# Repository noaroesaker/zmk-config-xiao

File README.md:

# zmk_corne

This project would not be possible without the help of these people:
https://github.com/makgyber/kiai-split
https://github.com/wj-zhe/Kretstrad
or most importantly:
https://github.com/alexpantiukhin/zmk-config-xiao
This one helped me figure out the layout for the files i need to make the firmware compile. It is modified, but the core of this persons work is still there, so thanks.

But lets not forget the best layout for custom keyboards :)
https://github.com/foostan/crkbd

And also the youtubers who helped me understand:
https://www.youtube.com/@joe_scotto
https://www.youtube.com/@SethusBuilds
https://www.youtube.com/@BenVallacksKeyboards
https://www.youtube.com/@BenVallack

This corne like build features a Xiao BLE controller and a custom designed board designed by me, but heavily inspired by the crkbd.
The wiring based on how the kiai split does it to keep both controllers up side but not use multiple pads like the older cornes or the helix

KiCad project is a redesigned corne choc, but everything is changed except the general outline. Files in this repository

The PCB did work, but there is some clearance issues with the power switch and the controller, so that will be changed in the kicad folder.

battery test:
10 nov 22:53:31 L = 3,89V R = 3,89V
+ 10:45 (battery connected) =
11 nov 09:46:10 L = 3,85V R = 3,86V
+ 02:30 (youtube usage) =
11 nov 12:15:10 L = 3,84V R = 3,85V
+ 01:30 (youtube and 10 min osu) =
11 nov 13:42:30 L = 3,83V R = 3,84V
+ 10:00 (disconnect battery) =
12 nov 11:48:30 L = 3,83V R = 3,85V
+ 08:45 (youtube usage) =
12 nov 20:27:30 L = 3,79V R = 3,82V

avrg loss
  L = 0,004V/h
  R = 0,003V/h

estimated battery life (4,1V - 3,2V = 0,9V)
  L = 0,9V / 0,004V = 225h = 9 days
  R = 0,9V / 0,003V = 300h = 12 days

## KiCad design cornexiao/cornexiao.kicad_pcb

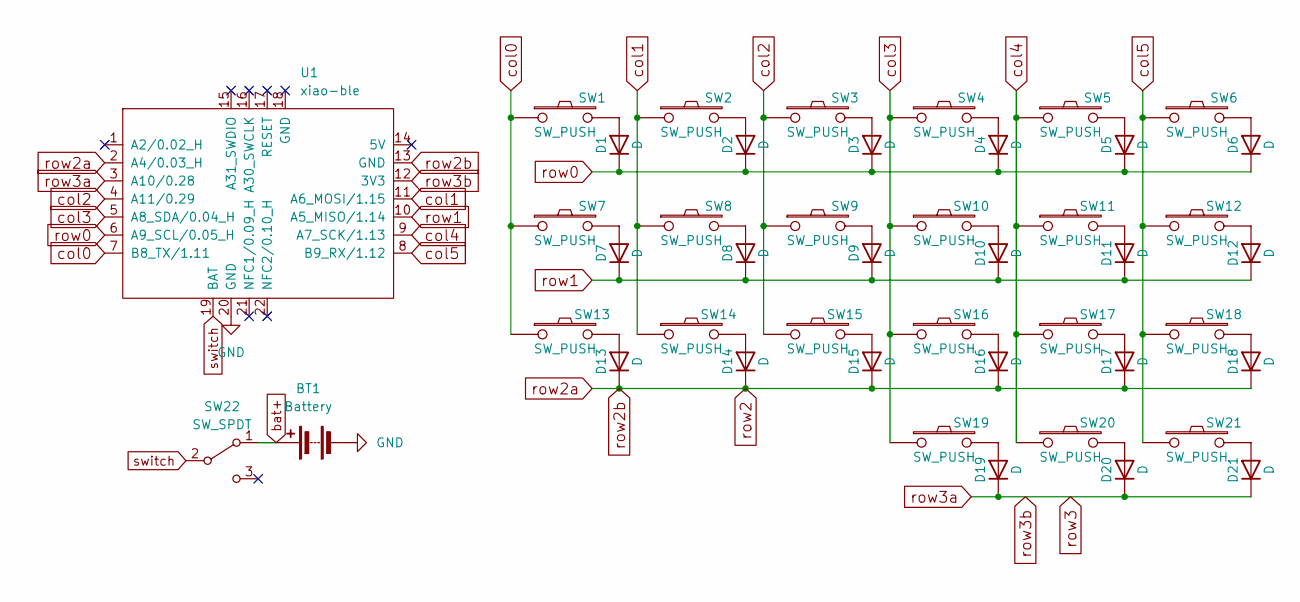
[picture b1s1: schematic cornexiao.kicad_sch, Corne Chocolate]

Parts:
BT1: Battery
D1, D2, D3, D4, D5, D6, D7, D8, D9, D10, D11, D12, D13, D14, D15, D16, D17, D18, D19, D20, D21: D; D3_TH_SMD
SW1, SW2, SW3, SW4, SW5, SW6, SW7, SW8, SW9, SW10, SW11, SW12, SW13, SW14, SW15, SW16, SW17, SW18, SW19, SW20, SW21: SW_PUSH; MX_ALPS_PG1350_noLed
SW22: SW_SPDT; SW_SPDT_PCM12
U1: xiao-ble; xiao-ble-smd-cutout

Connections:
GND: BT1.2 (-), U1.20 (GND)
unnamed: D1.2 (A), SW1.2
unnamed: D2.2 (A), SW2.2
unnamed: D3.2 (A), SW3.2
unnamed: D4.2 (A), SW4.2
unnamed: D5.2 (A), SW5.2
unnamed: D6.2 (A), SW6.2
unnamed: D7.2 (A), SW7.2
unnamed: D8.2 (A), SW8.2
unnamed: D9.2 (A), SW9.2
unnamed: D10.2 (A), SW10.2
unnamed: D11.2 (A), SW11.2
unnamed: D12.2 (A), SW12.2
unnamed: D13.2 (A), SW13.2
unnamed: D14.2 (A), SW14.2
unnamed: D15.2 (A), SW15.2
unnamed: D16.2 (A), SW16.2
unnamed: D17.2 (A), SW17.2
unnamed: D18.2 (A), SW18.2
unnamed: D19.2 (A), SW19.2
unnamed: D20.2 (A), SW20.2
unnamed: D21.2 (A), SW21.2
bat+: BT1.1 (+), SW22.1 (A); also elsewhere on the board
col0: SW1.1, SW7.1, SW13.1, U1.7 (B8_TX/1.11)
col1: SW2.1, SW8.1, SW14.1, U1.11 (A6_MOSI/1.15)
col2: SW3.1, SW9.1, SW15.1, U1.4 (A11/0.29)
col3: SW4.1, SW10.1, SW16.1, SW19.1, U1.5 (A8_SDA/0.04_H)
col4: SW5.1, SW11.1, SW17.1, SW20.1, U1.9 (A7_SCK/1.13)
col5: SW6.1, SW12.1, SW18.1, SW21.1, U1.8 (B9_RX/1.12)
row0: D1.1 (K), D2.1 (K), D3.1 (K), D4.1 (K), D5.1 (K), D6.1 (K), U1.6 (A9_SCL/0.05_H)
row1: D7.1 (K), D8.1 (K), D9.1 (K), D10.1 (K), D11.1 (K), D12.1 (K), U1.10 (A5_MISO/1.14)
row2: D13.1 (K), D14.1 (K), D15.1 (K), D16.1 (K), D17.1 (K), D18.1 (K), U1.2 (A4/0.03_H), U1.13 (GND); also elsewhere on the board
row3: D19.1 (K), D20.1 (K), D21.1 (K), U1.3 (A10/0.28), U1.12 (3V3); also elsewhere on the board
switch: SW22.2 (B), U1.19 (BAT); also elsewhere on the board

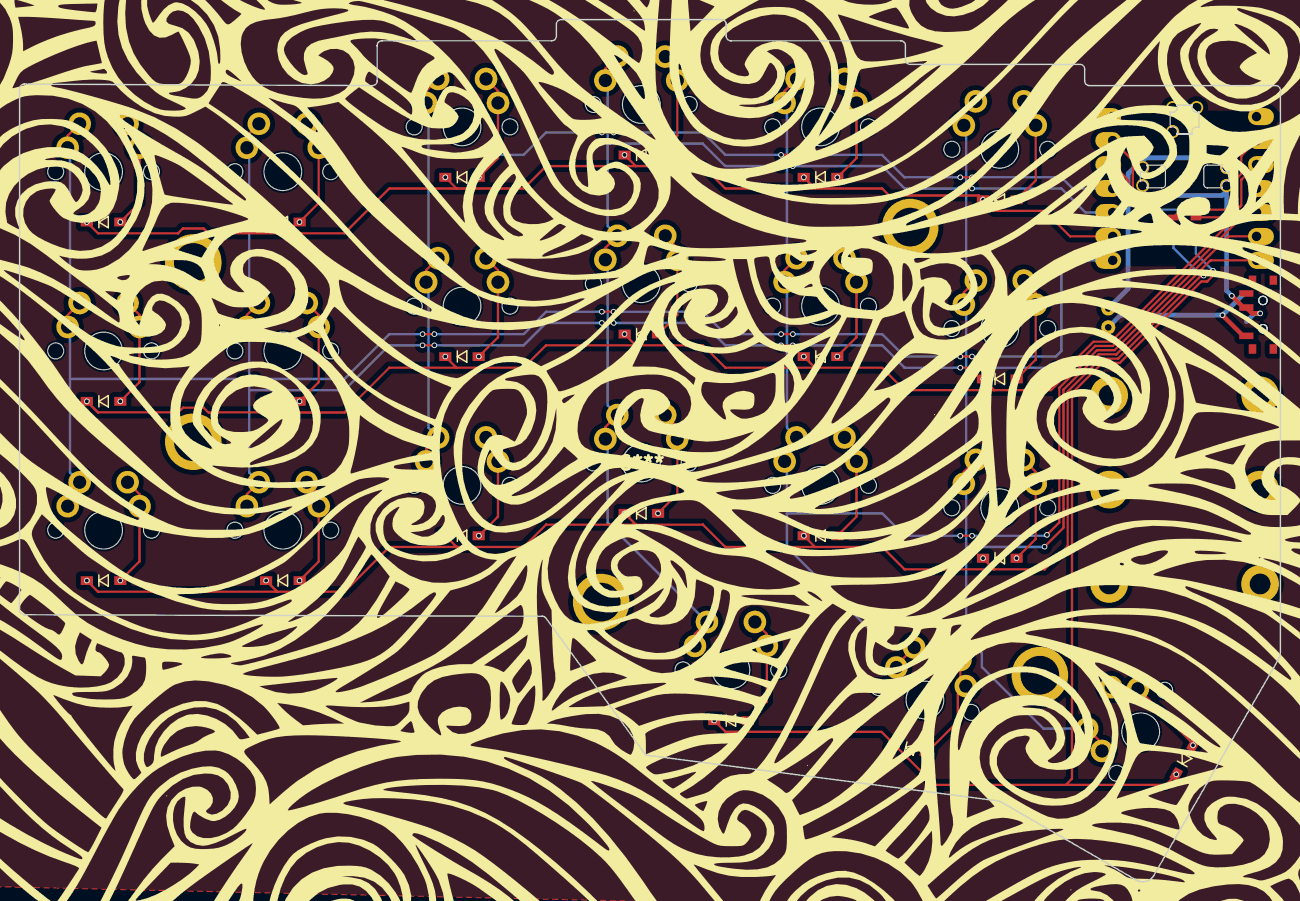
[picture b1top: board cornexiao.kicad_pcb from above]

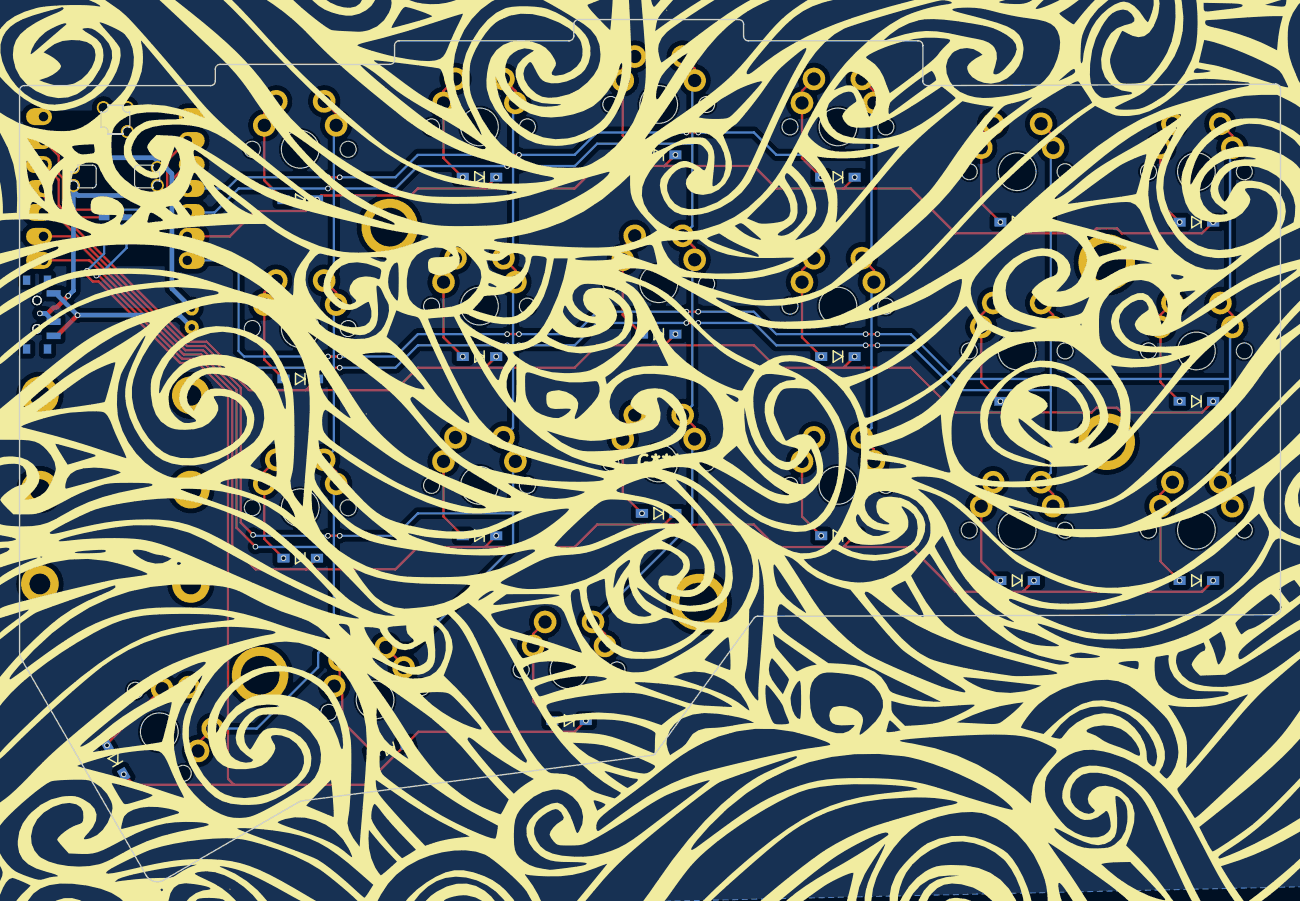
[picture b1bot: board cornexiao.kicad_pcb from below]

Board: 2 copper layers, 133.7 x 91.4 mm, 49 parts (3 on the bottom side), 33 nets.

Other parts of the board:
JP5, JP5#2, JP5#3, JP5#4: Jumper
SW22#2: SW_SPDT; SW_SPDT_PCM12

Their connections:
bat+: SW22#2.1 (A); also elsewhere on the board
row2: JP5.1, JP5.2, JP5#3.1, JP5#3.2; also elsewhere on the board
row3: JP5#2.1, JP5#2.2, JP5#4.1, JP5#4.2; also elsewhere on the board
switch: SW22#2.2 (B); also elsewhere on the board

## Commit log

2023-10-28 converting to corne
2023-10-28 added to kscan in dtsi
2023-10-28 Revert "converting to corne"
    This reverts commit 8bf1e7724f7523b571eb5557170040254e2c02a5.
2023-10-28 map change
2023-10-28 keymap
2023-10-28 moved kscan to overlays
    This reverts commit 701fc723fb2c14314905fe0f5fd61b7dbfa30ab2.
2023-10-28 rename to cornexiao
2023-10-28 forgot renaming board folder
2023-10-28 oh my days forgot renaming includes
2023-10-28 change pins to cornexiao based on kiai
2023-10-28 pins based on manuform
2023-10-28 pins changed to D0 - D10 instead of 1-11
2023-10-28 small touches. features and keymap next
2023-10-28 ordered pcb files
2023-10-28 updated file structure
2023-10-28 credits
2023-10-31 output expectations
2023-11-10 update in keymap
2023-11-10 keymap both ways?
2023-11-10 right update
2023-11-10 dont know where it takes effect, but dont matter
2023-11-10 small change in readme. 3d file refit next
2023-11-11 battery tests before testing disconnected state
2023-11-15 added reset bind resets
2023-11-15 prev push got stuck?
2023-11-15 oh my jays i saved myself
2023-11-22 longer before sleeping
2023-11-22 stepped down to one hour to sleep
2024-01-14 from trans to none
2024-01-14 added to outer keymap file
2024-01-14 hierarchy test
2024-01-14 test 2
2024-01-14 test 3
2024-01-14 test cleanup
2024-01-14 added back cause of some weirdness with numbers
2024-01-14 remvoed again for mor testing will elaborate
2024-01-14 added transparant where the layer changes happen
2024-01-14 changed layer change routes and added trans under landing zones
2024-07-21 Updated cornexiao.keymap
2024-11-03 refresh
2024-11-03 pics and shii
2024-11-03 last case file
2024-11-15 added zmk studio
2024-11-15 test
2024-11-15 test2
2024-11-15 Revert "added zmk studio"
    This reverts commit 7f22af25ef6657785963dc0c6ce6378cb60ad8f1.
2024-11-15 Revert "test2"
    This reverts commit 4f3205c304a8c123ec5185f267d21f5e2e75fc9c.
2024-11-15 Revert "test"
    This reverts commit f0386cd32084b20726bd3753b05ea435e6dd107b.
2024-11-16 hopeful test
2024-11-16 frogot
2024-11-16 both?
2024-11-16 nhow?
2024-11-16 aint gonna woek fewlla
2024-11-16 works with app at least. working to fix right half
2024-11-16 bi changes
2024-11-16 ommyjays
2024-11-16 perif1
2024-11-16 kconfiug?
2024-11-16 onoly oproblems with left side like wtf
2024-11-17 test maybe
2024-11-17 logging
2024-11-17 unsure of format
2024-11-17 this one
2024-11-17 var jegon god helt fjern?
2024-11-17 oduble
2024-11-17 ig change
2024-11-17 yeeah
2024-11-17 ionnow anymore
2024-11-17 another pos map
2024-11-17 asdf
2024-11-17 boutta change whole
2024-11-17 whtyamean
2024-11-17 big changes again (copy maybe correct shit)
2024-11-17 remove unused
2024-11-17 wonmg spo å
